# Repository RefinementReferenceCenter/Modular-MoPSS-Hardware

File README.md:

# Modular-MoPSS-Hardware

This repository contains the necessary files for 3D printing and to order the ModMoPSS module PCBs (eagle)

(This is a work in progress)

The contents of this repository are distributed under the GNU General Public License v3.0

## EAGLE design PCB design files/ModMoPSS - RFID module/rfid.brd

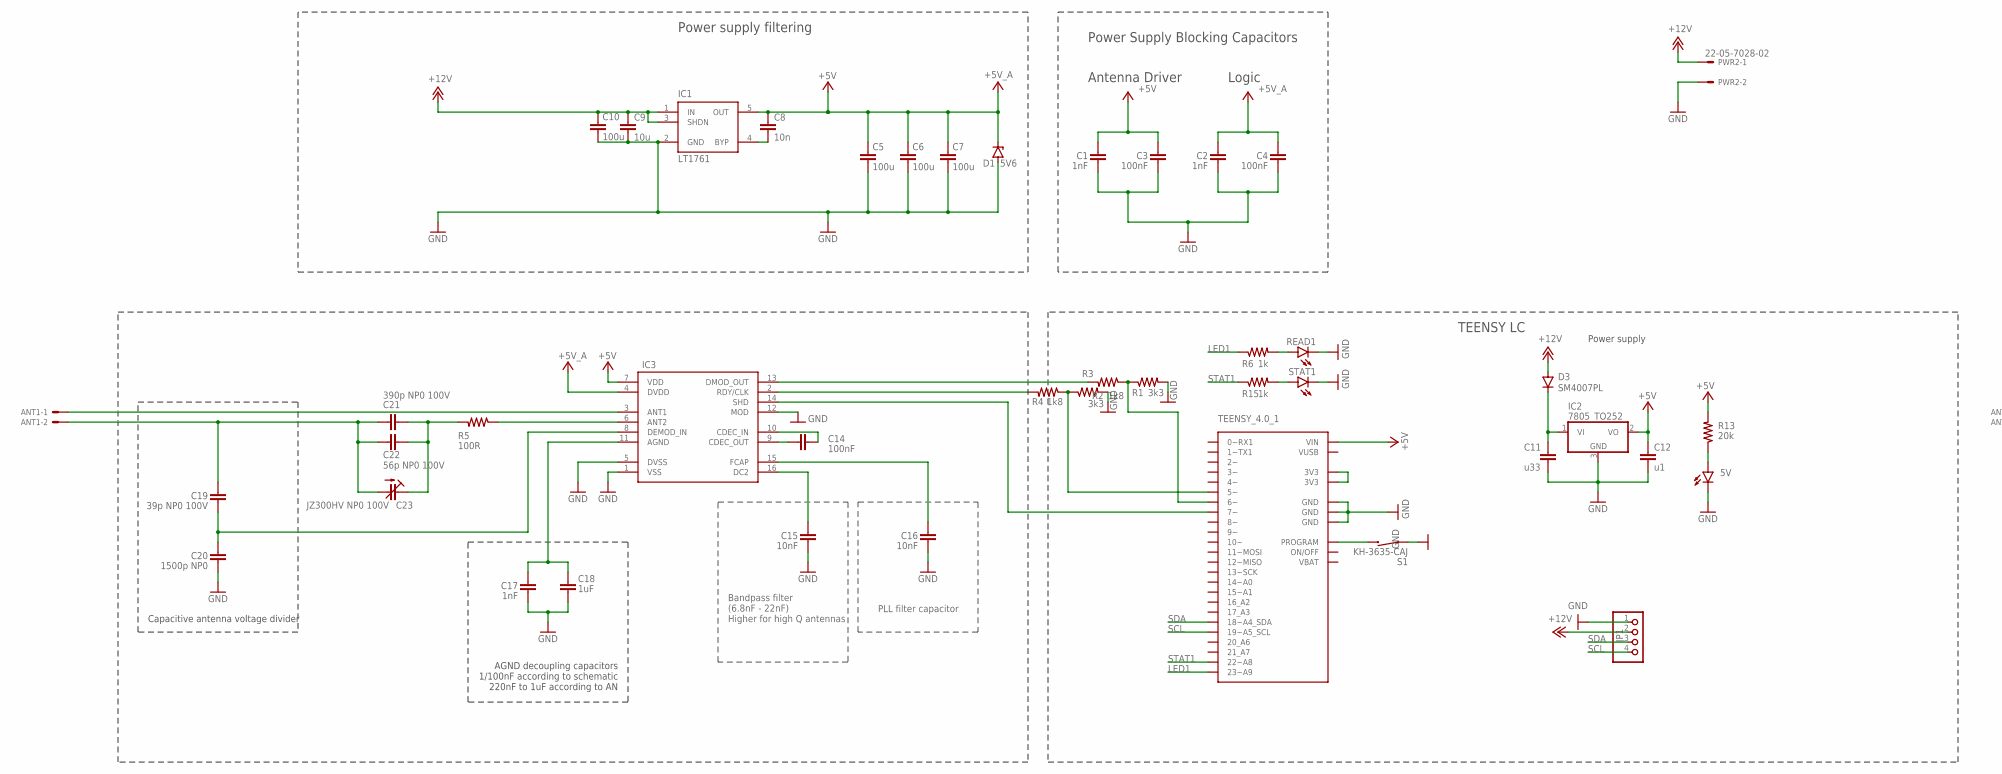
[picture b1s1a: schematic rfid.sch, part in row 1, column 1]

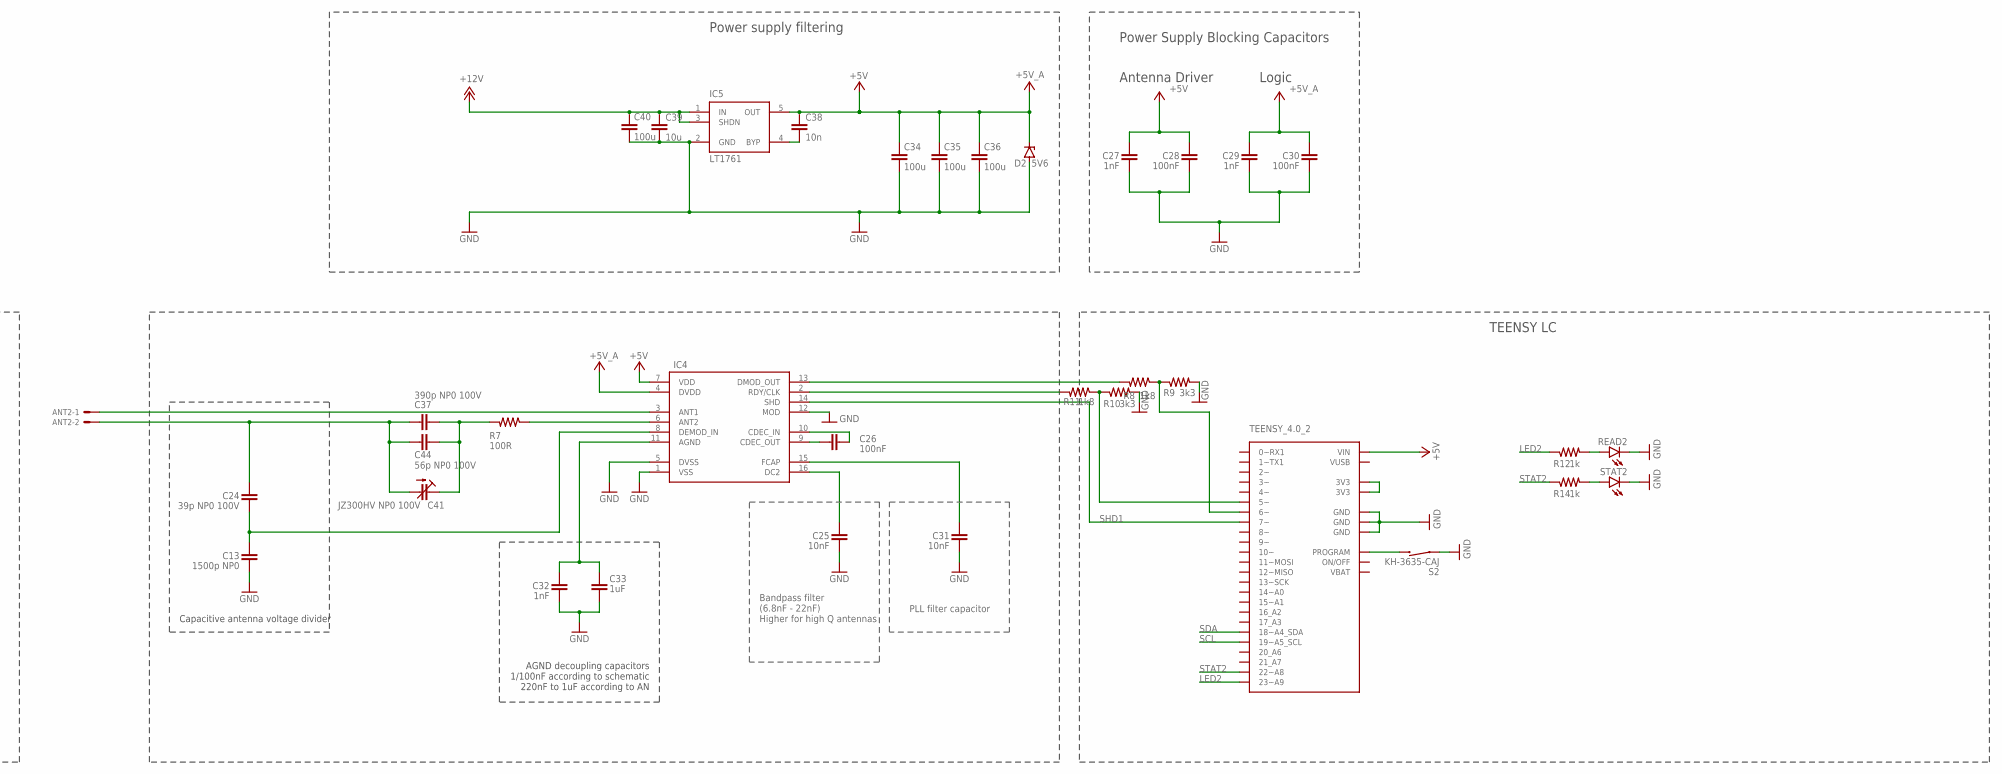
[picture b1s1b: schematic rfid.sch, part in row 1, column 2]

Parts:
5V: LEDCHIPLED_0805; CHIPLED_0805
ANT1, ANT2: 53261-02
C1, C2, C17, C27, C29, C32: 1nF; R1206
C3, C4, C14, C26, C28, C30: 100nF; R1206
C5, C6, C7, C10, C34, C35, C36, C40: 100u; R1206
C8, C38: 10n; R1206
C9, C39: 10u; R1206
C11: u33; C0805
C12: u1; C0805
C13, C20: 1500p NP0; R1206
C15, C16, C25, C31: 10nF; R1206
C18, C33: 1uF; R1206
C19, C24: 39p NP0 100V; R1206
C21, C37: 390p NP0 100V; R1206
C22, C44: 56p NP0 100V; R1206
C23, C41: JZ300HV NP0 100V; JZ300HV
D1, D2: 5V6; SOD80C
D3: SM4007PL; SOD-123_MINI-SMA
IC1, IC5: LT1761; TSOT23-5
IC2: 7805_TO252; TO252
IC3, IC4: EM4095; SO16
JP1: PINHD-1X4; 1X04
PWR2: 22-05-7028-02; 7395-02
R1, R3, R9, R10: 3k3; R0805
R2, R4, R8, R11: 1k8; R0805
R5, R7: 100R; R1206
R6, R12, R14, R15: 1k; R0805
R13: 20k; R0805
READ1, READ2: LEDCHIPLED_0805; CHIPLED_0805
S1, S2: KH-3635-CAJ
STAT1, STAT2: LEDCHIPLED_0805; CHIPLED_0805
TEENSY_4.0_1, TEENSY_4.0_2: TEENSY40

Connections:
+5V: C1.2, C2.2, C3.2, C4.2, C5.1, C6.1, C7.1, C8.1, C12.1, C27.2, C28.2, C29.2, C30.2, C34.1, C35.1, C36.1, C38.1, D1.C, D2.C, IC1.5 (OUT), IC2.2 (VO), IC3.4 (DVDD), IC3.7 (VDD), IC4.4 (DVDD), IC4.7 (VDD), IC5.5 (OUT), R13.2, TEENSY_4.0_1.VIN, TEENSY_4.0_2.VIN
+12V: C9.1, C10.1, C39.1, C40.1, D3.A, IC1.1 (IN), IC1.3 (SHDN), IC5.1 (IN), IC5.3 (SHDN), JP1.2, PWR2.1
AGND: C17.2, C18.2, IC3.11 (AGND)
AGND1: C32.2, C33.2, IC4.11 (AGND)
ANT2: IC3.6 (ANT2), R5.1
ANT3: IC4.6 (ANT2), R7.1
ANT4: ANT2.1, IC4.3 (ANT1)
CDEC_IN: C14.2, IC3.10 (CDEC_IN)
CDEC_IN1: C26.2, IC4.10 (CDEC_IN)
CDEC_OUT: C14.1, IC3.9 (CDEC_OUT)
CDEC_OUT1: C26.1, IC4.9 (CDEC_OUT)
DC1: C25.1, IC4.16 (DC2)
DC2: C15.1, IC3.16 (DC2)
DMODI: C19.1, C20.2, IC3.8 (DEMOD_IN)
DMODI1: C13.2, C24.1, IC4.8 (DEMOD_IN)
FCAP: C16.1, IC3.15 (FCAP)
FCAP1: C31.1, IC4.15 (FCAP)
GND: 5V.C, C1.1, C2.1, C3.1, C4.1, C5.2, C6.2, C7.2, C9.2, C10.2, C11.2, C12.2, C13.1, C15.2, C16.2, C17.1, C18.1, C20.1, C25.2, C27.1, C28.1, C29.1, C30.1, C31.2, C32.1, C33.1, C34.2, C35.2, C36.2, C39.2, C40.2, D1.A, D2.A, IC1.2 (GND), IC2.3 (GND), IC3.1 (VSS), IC3.5 (DVSS), IC3.12 (MOD), IC4.1 (VSS), IC4.5 (DVSS), IC4.12 (MOD), IC5.2 (GND), JP1.1, PWR2.2, R1.2, R3.2, R9.2, R10.2, READ1.C, READ2.C, S1.P$1 (1), S2.P$1 (1), STAT1.C, STAT2.C, TEENSY_4.0_1.GND, TEENSY_4.0_1.GND@1 (GND), TEENSY_4.0_1.GND@2 (GND), TEENSY_4.0_2.GND, TEENSY_4.0_2.GND@1 (GND), TEENSY_4.0_2.GND@2 (GND)
LED1: R6.1, TEENSY_4.0_1.23 (23~A9)
LED2: R12.1, TEENSY_4.0_2.23 (23~A9)
unnamed: R6.2, READ1.A
unnamed: R3.1, R4.1, TEENSY_4.0_1.5 (5~)
unnamed: ANT2.2, C24.2, C37.1, C41.P$1 (A), C44.1
unnamed: C37.2, C41.P$2 (E), C44.2, R7.2
unnamed: C21.2, C22.2, C23.P$2 (E), R5.2
unnamed: R1.1, R2.1, TEENSY_4.0_1.6 (6~)
unnamed: C8.2, IC1.4 (BYP)
unnamed: S1.P$2 (2), TEENSY_4.0_1.PROG (PROGRAM)
unnamed: C38.2, IC5.4 (BYP)
unnamed: TEENSY_4.0_1.3V3, TEENSY_4.0_1.3V3@2 (3V3)
unnamed: R8.1, R9.1, TEENSY_4.0_2.6 (6~)
unnamed: R10.1, R11.1, TEENSY_4.0_2.5 (5~)
unnamed: R12.2, READ2.A
unnamed: ANT1.2, C19.2, C21.1, C22.1, C23.P$1 (A)
unnamed: IC3.14 (SHD), TEENSY_4.0_1.7 (7~)
unnamed: S2.P$2 (2), TEENSY_4.0_2.PROG (PROGRAM)
unnamed: TEENSY_4.0_2.3V3, TEENSY_4.0_2.3V3@2 (3V3)
unnamed: R14.2, STAT2.A
unnamed: R15.2, STAT1.A
unnamed: ANT1.1, IC3.3 (ANT1)
unnamed: C11.1, D3.C, IC2.1 (VI)
unnamed: IC4.13 (DMOD_OUT), R8.2
unnamed: IC3.2 (RDY/CLK), R4.2
unnamed: IC3.13 (DMOD_OUT), R2.2
unnamed: 5V.A, R13.1
unnamed: IC4.2 (RDY/CLK), R11.2
SCL: JP1.4, TEENSY_4.0_1.19 (19~A5_SCL), TEENSY_4.0_2.19 (19~A5_SCL)
SDA: JP1.3, TEENSY_4.0_1.18 (18~A4_SDA), TEENSY_4.0_2.18 (18~A4_SDA)
SHD1: IC4.14 (SHD), TEENSY_4.0_2.7 (7~)
STAT1: R15.1, TEENSY_4.0_1.22 (22~A8)
STAT2: R14.1, TEENSY_4.0_2.22 (22~A8)

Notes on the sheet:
Power supply filtering
Antenna Driver
Logic
AGND decoupling capacitors 1/100nF according to schematic 220nF to 1uF according to AN
Capacitive antenna voltage divider
Bandpass filter (6.8nF - 22nF) Higher for high Q antennas
PLL filter capacitor
Power Supply Blocking Capacitors
TEENSY LC
Power supply

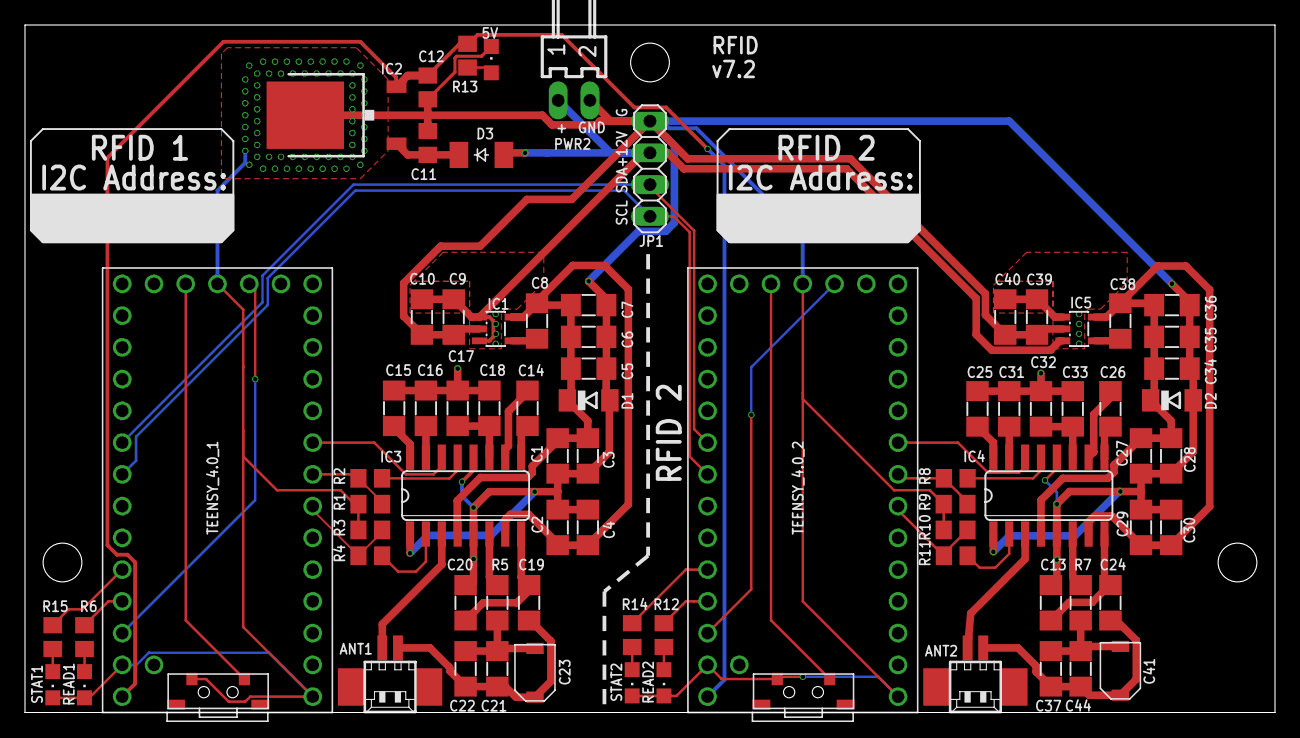
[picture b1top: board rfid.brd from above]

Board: 2 copper layers, 100.0 x 55.0 mm, 78 parts (0 on the bottom side), 51 nets.

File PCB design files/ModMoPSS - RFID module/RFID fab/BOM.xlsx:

Comment | Designator | Footprint | JLCPCB Part #（optional）
red | 5V, READ1, READ2, STAT1, STAT2 | CHIPLED_0805 | C84256
100R 100V | R5, R7 | R1206 | C17901
100nF | C3, C4, C14, C26, C28, C30 | R1206 | C24497
100u 6.3V | C5, C6, C7, C10, C34, C35, C36, C40 | R1206 | C15008
10n | C8, C38 | R1206 | C1846
10nF | C15, C16, C25, C31 | R1206 | C1846
10u 16V | C9, C39 | R1206 | C2911415
1500p NP0 | C13, C20 | R1206 | C309500
1k | R6, R12, R14, R15 | R0805 | C17513
1k8 | R2, R4, R8, R11 | R0805 | C17398
1nF | C1, C2, C17, C27, C29, C32 | R1206 | C9196
1uF | C18, C33 | R1206 | C1848
20k | R13 | R0805 | C4328
390p NP0 100V | C21, C37 | R1206 | C527300
39p NP0 100V | C19, C24 | R1206 | C527287
3k3 | R1, R3, R9, R10 | R0805 | C26010
53048-02 | ANT1, ANT2 | 53048-02 | C505099
56p NP0 100V | C22, C44 | R1206 | C527289
5V6 | D1, D2 | SOD80C | C8062
7805_TO252 | IC2 | TO252 | C233417
EM4095 | IC3, IC4 | SO16 | C11356
JZ300HV | C23, C41 | JZ300HV
KH-3635-CAJ | S1, S2 | KH-3635-CAJ | C530670
LT1761ES5-5 | IC1, IC5 | TSOT23-5 | C117230
u1 | C12 | C0805 | C49678
u33 | C11 | C0805 | C1740

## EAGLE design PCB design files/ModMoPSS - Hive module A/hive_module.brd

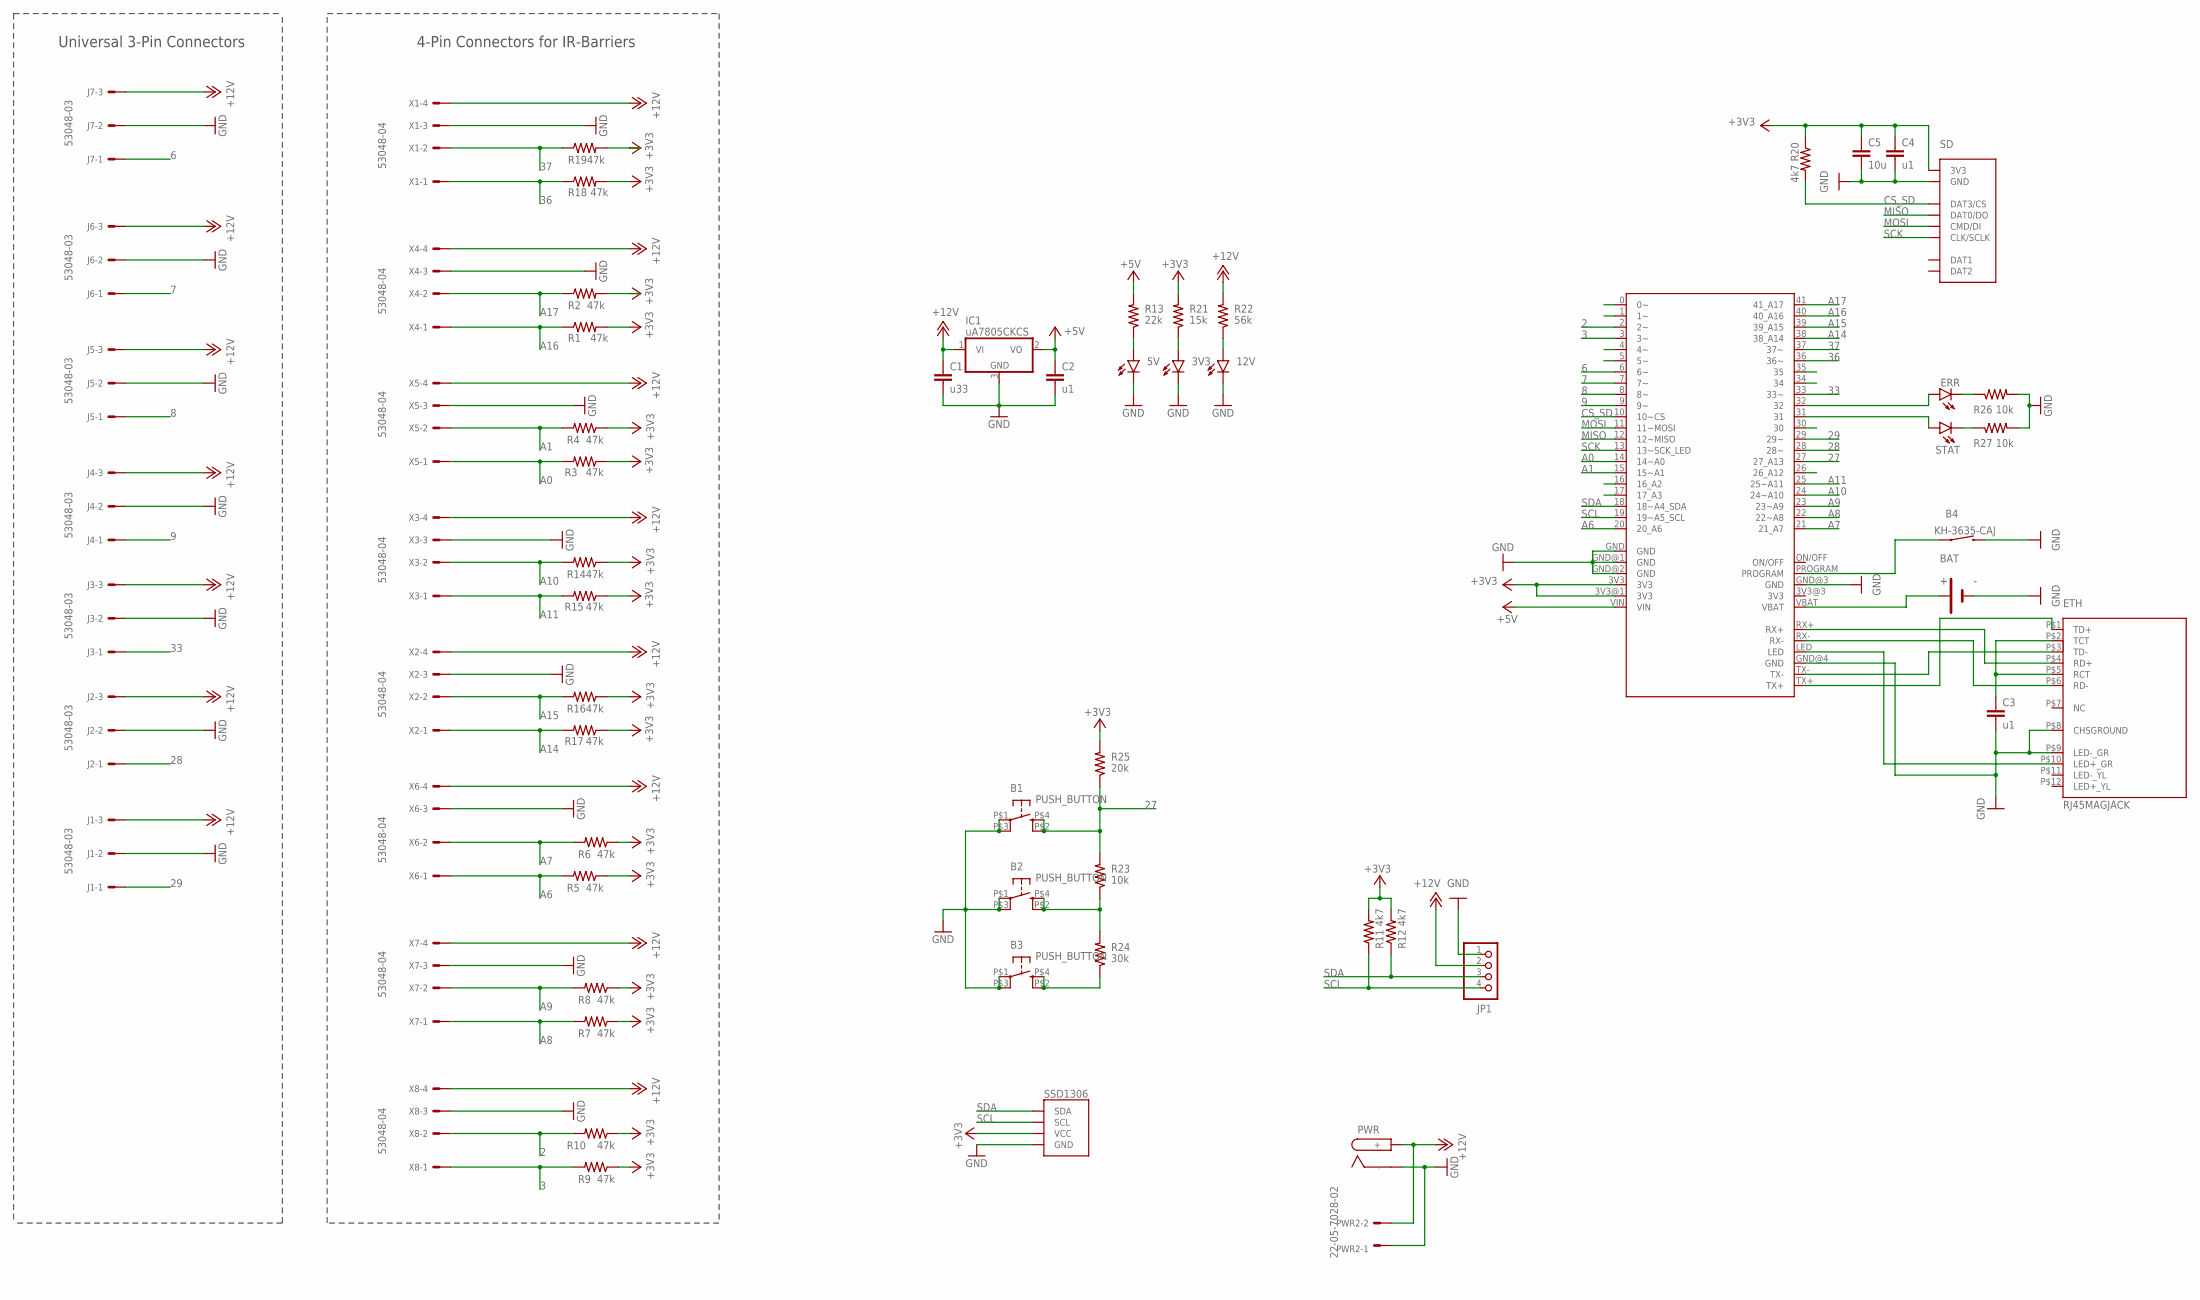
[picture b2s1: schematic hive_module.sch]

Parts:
3V3, 5V, 12V: LEDCHIP-LED0805; CHIP-LED0805
B1, B2, B3: PUSH_BUTTON
B4: KH-3635-CAJ
BAT: BS-08-B2AA002
C1: u33; C0805
C2, C3, C4: u1; C0805
C5: 10u; C0805
ERR: LEDCHIP-LED0805; CHIP-LED0805
ETH: RJ45MAGJACK; LPJ4012AHNL
IC1: uA7805CKCS; TO252
J1, J2, J3, J4, J5, J6, J7: 53048-03
JP1: PINHD-1X4; 1X04
PWR: DC-042C-Z-2.5-A
PWR2: 22-05-7028-02; 7395-02
R1, R2, R3, R4, R5, R6, R7, R8, R9, R10, R14, R15, R16, R17, R18, R19: 47k; R0805
R11, R12, R20: 4k7; R0805
R13: 22k; R0805
R21: 15k; R0805
R22: 56k; R0805
R23, R26, R27: 10k; R0805
R24: 30k; R0805
R25: 20k; R0805
SD: TF-011
SSD1306: SSD1306
STAT: LEDCHIP-LED0805; CHIP-LED0805
U$1: TEENSY41
X1, X2, X3, X4, X5, X6, X7, X8: 53048-04

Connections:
2: R10.2, U$1.2 (2~), X8.2
3: R9.2, U$1.3 (3~), X8.1
6: J7.1, U$1.6 (6~)
7: J6.1, U$1.7 (7~)
8: J5.1, U$1.8 (8~)
9: J4.1, U$1.9 (9~)
27: B1.P$2 (S1), B1.P$4 (S), R23.2, R25.1, U$1.27 (27_A13)
28: J2.1, U$1.28 (28~)
29: J1.1, U$1.29 (29~)
33: J3.1, U$1.33 (33~)
36: R18.1, U$1.36 (36~), X1.1
37: R19.1, U$1.37 (37~), X1.2
+3V3: C4.1, C5.1, R1.2, R2.2, R3.1, R4.1, R5.1, R6.1, R7.1, R8.1, R9.1, R10.1, R11.2, R12.2, R14.1, R15.1, R16.1, R17.1, R18.2, R19.2, R20.1, R21.2, R25.2, SD.P$4 (3V3), SSD1306.P$2 (VCC), U$1.3V3, U$1.3V3@1 (3V3)
+5V: C2.1, IC1.2 (VO), R13.2, U$1.VIN
+12V: C1.1, IC1.1 (VI), J1.3, J2.3, J3.3, J4.3, J5.3, J6.3, J7.3, JP1.2, PWR.P$6 (+), PWR2.2, R22.2, X1.4, X2.4, X3.4, X4.4, X5.4, X6.4, X7.4, X8.4
A0: R3.2, U$1.14 (14~A0), X5.1
A1: R4.2, U$1.15 (15~A1), X5.2
A6: R5.2, U$1.20 (20_A6), X6.1
A7: R6.2, U$1.21 (21_A7), X6.2
A8: R7.2, U$1.22 (22~A8), X7.1
A9: R8.2, U$1.23 (23~A9), X7.2
A10: R14.2, U$1.24 (24~A10), X3.2
A11: R15.2, U$1.25 (25~A11), X3.1
A14: R17.2, U$1.38 (38_A14), X2.1
A15: R16.2, U$1.39 (39_A15), X2.2
A16: R1.1, U$1.40 (40_A16), X4.1
A17: R2.1, U$1.41 (41_A17), X4.2
CS_SD: R20.2, SD.P$2 (DAT3/CS), U$1.10 (10~CS)
GND: 3V3.C, 5V.C, 12V.C, B1.P$1, B1.P$3 (P1), B2.P$1, B2.P$3 (P1), B3.P$1, B3.P$3 (P1), B4.P$2 (2), BAT.-, C1.2, C2.2, C3.2, C4.2, C5.2, ETH.P$8 (CHSGROUND), ETH.P$9 (LED-_GR), IC1.3 (GND), J1.2, J2.2, J3.2, J4.2, J5.2, J6.2, J7.2, JP1.1, PWR.P$1 (-), PWR.P$2 (-), PWR.P$3 (-), PWR.P$4 (-), PWR.P$5 (-), PWR2.1, R26.2, R27.2, SD.P$6 (GND), SD.P$9 (GND), SD.P$10 (GND), SD.P$11 (GND), SD.P$12 (GND), SSD1306.P$1 (GND), U$1.GND, U$1.GND@1 (GND), U$1.GND@2 (GND), U$1.GND@3 (GND), U$1.GND@4 (GND), X1.3, X2.3, X3.3, X4.3, X5.3, X6.3, X7.3, X8.3
MISO: SD.P$7 (DAT0/DO), U$1.12 (12~MISO)
MOSI: SD.P$3 (CMD/DI), U$1.11 (11~MOSI)
unnamed: ETH.P$1 (TD+), U$1.TX+
unnamed: ETH.P$3 (TD-), U$1.TX-
unnamed: 3V3.A, R21.1
unnamed: ETH.P$6 (RD-), U$1.RX-
unnamed: ETH.P$4 (RD+), U$1.RX+
unnamed: ETH.P$10 (LED+_GR), U$1.LED
unnamed: 12V.A, R22.1
unnamed: C3.1, ETH.P$2 (TCT), ETH.P$5 (RCT)
unnamed: BAT.+, U$1.VBAT
unnamed: B4.P$1 (1), U$1.PROGRAM
unnamed: ERR.A, U$1.32
unnamed: B3.P$2 (S1), B3.P$4 (S), R24.1
unnamed: B2.P$2 (S1), B2.P$4 (S), R23.1, R24.2
unnamed: ERR.C, R26.1
unnamed: R27.1, STAT.C
unnamed: STAT.A, U$1.31
unnamed: 5V.A, R13.1
SCK: SD.P$5 (CLK/SCLK), U$1.13 (13~SCK_LED)
SCL: JP1.4, R11.1, SSD1306.P$3 (SCL), U$1.19 (19~A5_SCL)
SDA: JP1.3, R12.1, SSD1306.P$4 (SDA), U$1.18 (18~A4_SDA)

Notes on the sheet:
4-Pin Connectors for IR-Barriers
Universal 3-Pin Connectors

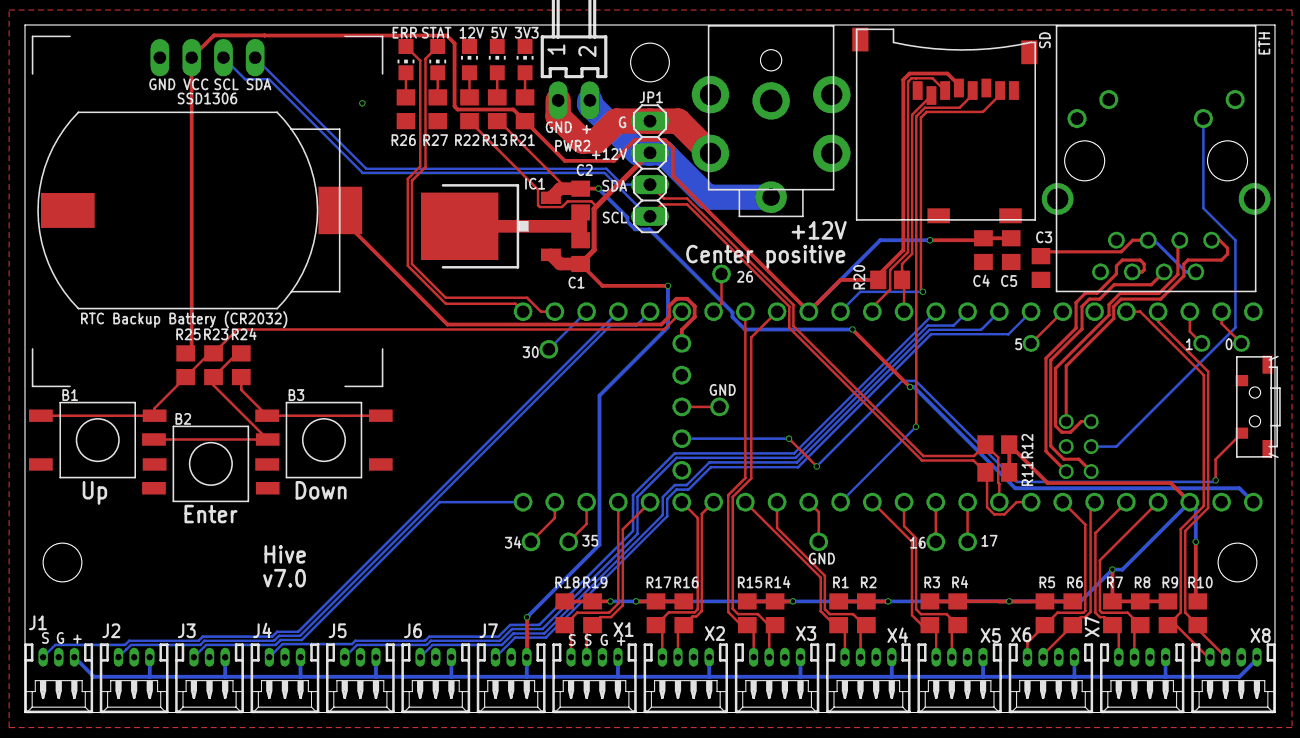
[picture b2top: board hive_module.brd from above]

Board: 2 copper layers, 100.0 x 55.0 mm, 65 parts (0 on the bottom side), 51 nets.

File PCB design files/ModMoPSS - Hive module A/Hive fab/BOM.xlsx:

Comment | Designator | Footprint | JLCPCB Part #（optional）
red | 3V3, 5V, 12V, ERR, STAT | CHIP-LED0805 | C84256
10k | R23, R26, R27 | R0805 | C17414
10u | C5 | C0805 | C15850
15k | R21 | R0805 | C17475
20k | R25 | R0805 | C4328
22k | R13 | R0805 | C17475
30k | R24 | R0805 | C17621
47k | R1, R2, R3, R4, R5, R6, R7, R8, R9, R10, R14, R15, R16, R17, R18, R19 | R0805 | C17713
4k7 | R11, R12, R20 | R0805 | C17673
53048-03 | J1, J2, J3, J4, J5, J6, J7 | 53048-03 | C505275
53048-04 | X1, X2, X3, X4, X5, X6, X7, X8 | 53048-04 | C588275
56k | R22 | R0805 | C17756
BS-08-B2AA002 | BAT | BS-08-B2AA002 | C964790
DC-042C-Z-2.5-A | PWR | DC-042C-Z-2.5-A | C706901
KH-3635-CAJ | B4 | KH-3635-CAJ | C530670
PUSH_BUTTON | B1, B2, B3 | PUSH_BUTTON | C127507
RJ45MAGJACK | ETH | LPJ4012AHNL | C910371
SSD1306 | SSD1306 | SSD1306 | C2718488
TF-011 | SD | TF-011 | C410352
u1 | C2, C3, C4 | C0805 | C49678
u33 | C1 | C0805 | C1740
uA7805CKCS | IC1 | TO252 | C233417

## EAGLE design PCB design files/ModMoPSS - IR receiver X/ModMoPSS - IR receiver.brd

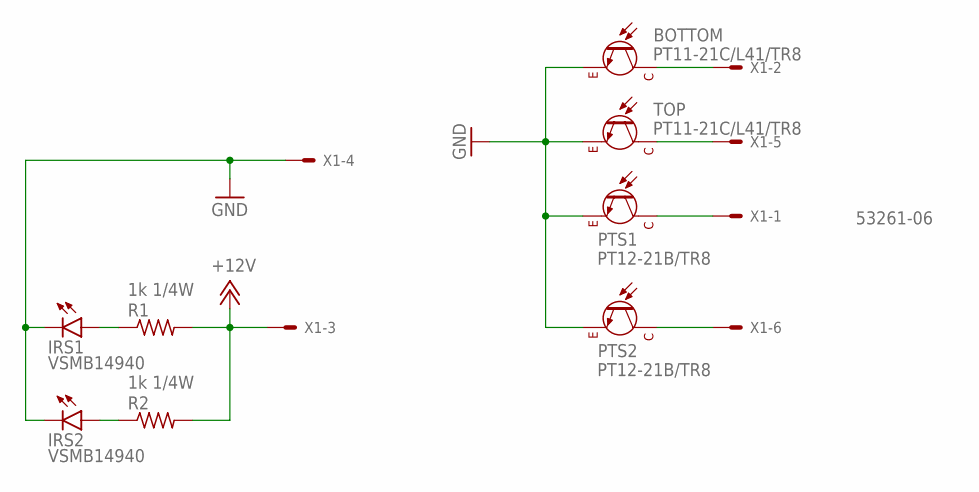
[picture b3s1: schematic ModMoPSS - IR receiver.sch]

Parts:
BOTTOM: PT11-21C/L41/TR8; CHIPLED_1206
IRS1, IRS2: VSMB14940
PTS1, PTS2: PT12-21B/TR8
R1, R2: 1k 1/4W; R0805
TOP: PT11-21C/L41/TR8; CHIPLED_1206
X1: 53261-06

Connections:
+12V: R1.2, R2.2, X1.3
GND: BOTTOM.A (E), IRS1.P$2 (C), IRS2.P$2 (C), PTS1.P$2 (E), PTS2.P$2 (E), TOP.A (E), X1.4
unnamed: BOTTOM.C, X1.2
unnamed: PTS1.P$1 (C), X1.1
unnamed: TOP.C, X1.5
unnamed: IRS2.P$1 (A), R2.1
unnamed: PTS2.P$1 (C), X1.6
unnamed: IRS1.P$1 (A), R1.1

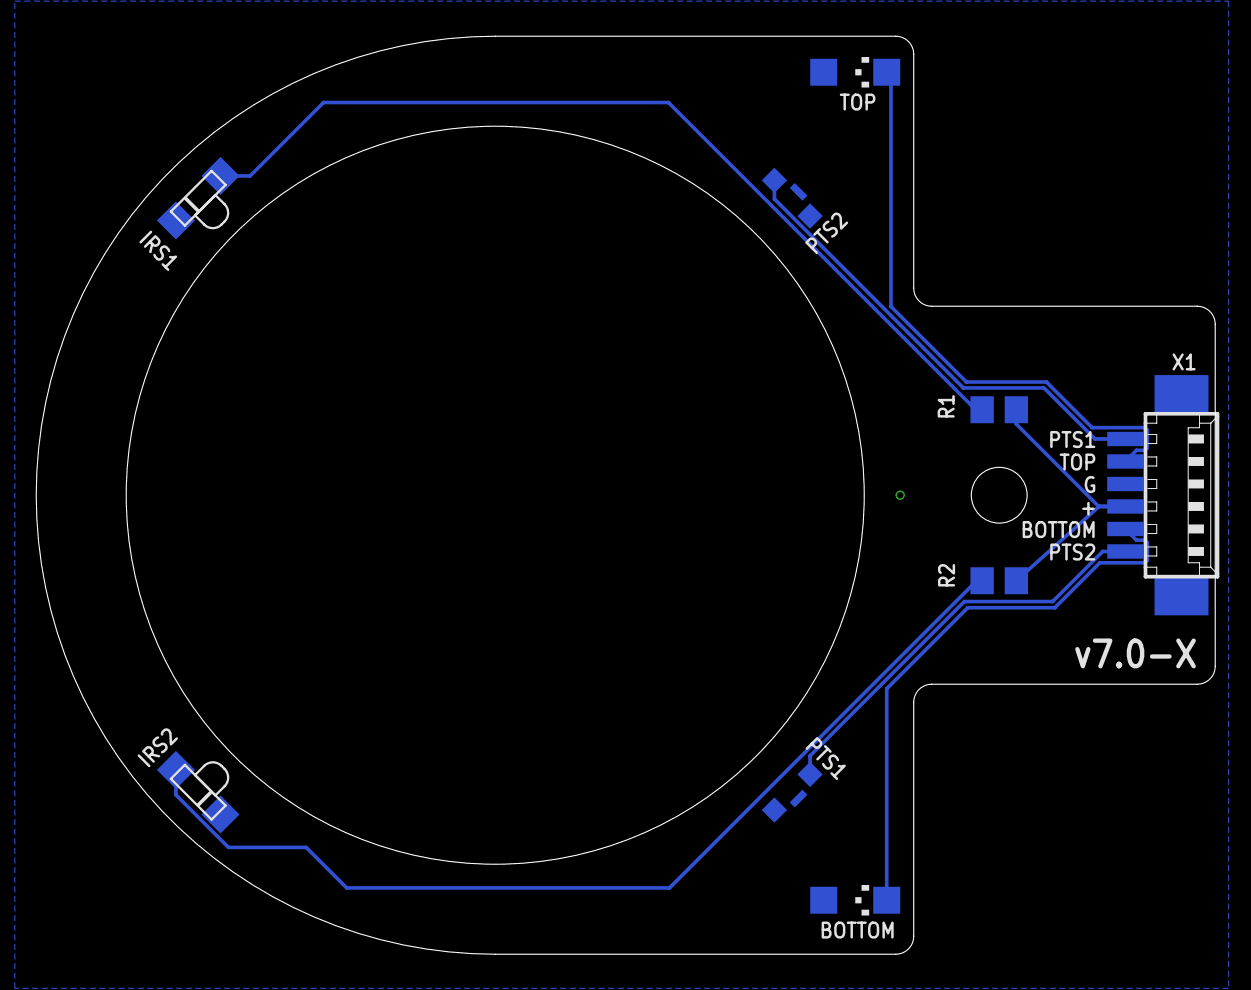
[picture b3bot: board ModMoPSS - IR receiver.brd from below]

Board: 2 copper layers, 65.5 x 51.0 mm, 9 parts (9 on the bottom side), 8 nets.

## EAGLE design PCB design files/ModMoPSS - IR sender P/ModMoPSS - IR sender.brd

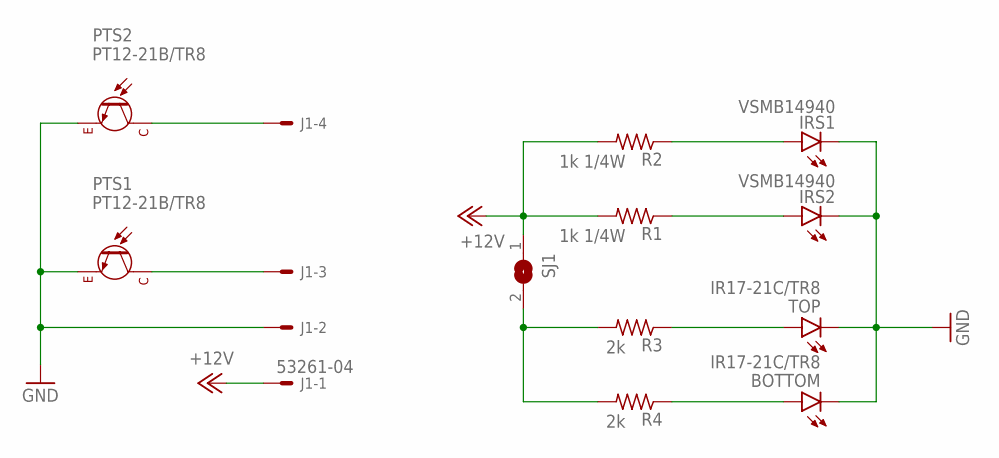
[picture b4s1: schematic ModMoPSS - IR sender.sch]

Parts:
BOTTOM: IR17-21C/TR8; CHIP-LED0805
IRS1, IRS2: VSMB14940
J1: 53261-04
PTS1, PTS2: PT12-21B/TR8
R1, R2: 1k 1/4W; R0805
R3, R4: 2k; R0805
SJ1: SJ
TOP: IR17-21C/TR8; CHIP-LED0805

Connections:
+12V: J1.1, R1.2, R2.2, SJ1.1
GND: BOTTOM.C, IRS1.P$2 (C), IRS2.P$2 (C), J1.2, PTS1.P$2 (E), PTS2.P$2 (E), TOP.C
unnamed: J1.3, PTS1.P$1 (C)
unnamed: IRS1.P$1 (A), R2.1
unnamed: BOTTOM.A, R4.1
unnamed: R3.1, TOP.A
unnamed: J1.4, PTS2.P$1 (C)
unnamed: R3.2, R4.2, SJ1.2
unnamed: IRS2.P$1 (A), R1.1

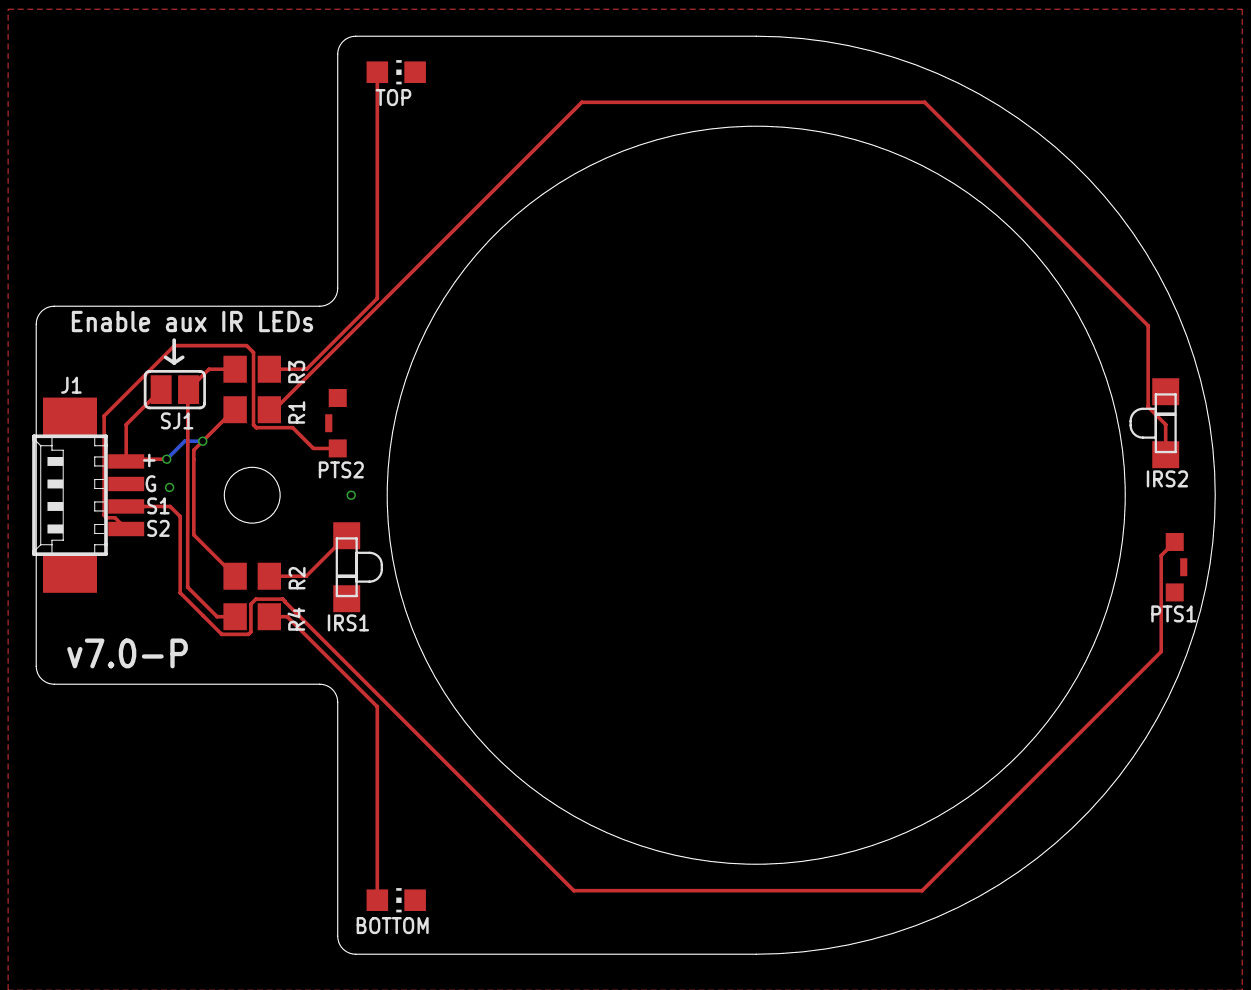
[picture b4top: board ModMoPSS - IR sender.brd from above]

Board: 2 copper layers, 65.5 x 51.0 mm, 12 parts (0 on the bottom side), 9 nets.

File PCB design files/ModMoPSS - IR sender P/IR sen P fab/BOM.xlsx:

Comment | Designator | Footprint | JLCPCB Part #（optional）
IR17-21C/TR8 | BOTTOM | CHIP-LED0805 | C131250
VSMB14940 | IRS1 | VSMB14940 | C511069
VSMB14940 | IRS2 | VSMB14940 | C511069
53261-04 | J1 | 53261-04 | C127368
PT12-21B/TR8 | PTS1 | PT12-21B/TR8 | C264383
PT12-21B/TR8 | PTS2 | PT12-21B/TR8 | C264383
1k 1/4W | R1 | R0805 | C412430
1k 1/4W | R2 | R0805 | C412430
2k | R3 | R0805 | C17604
2k | R4 | R0805 | C17604
IR17-21C/TR8 | TOP | CHIP-LED0805 | C131250

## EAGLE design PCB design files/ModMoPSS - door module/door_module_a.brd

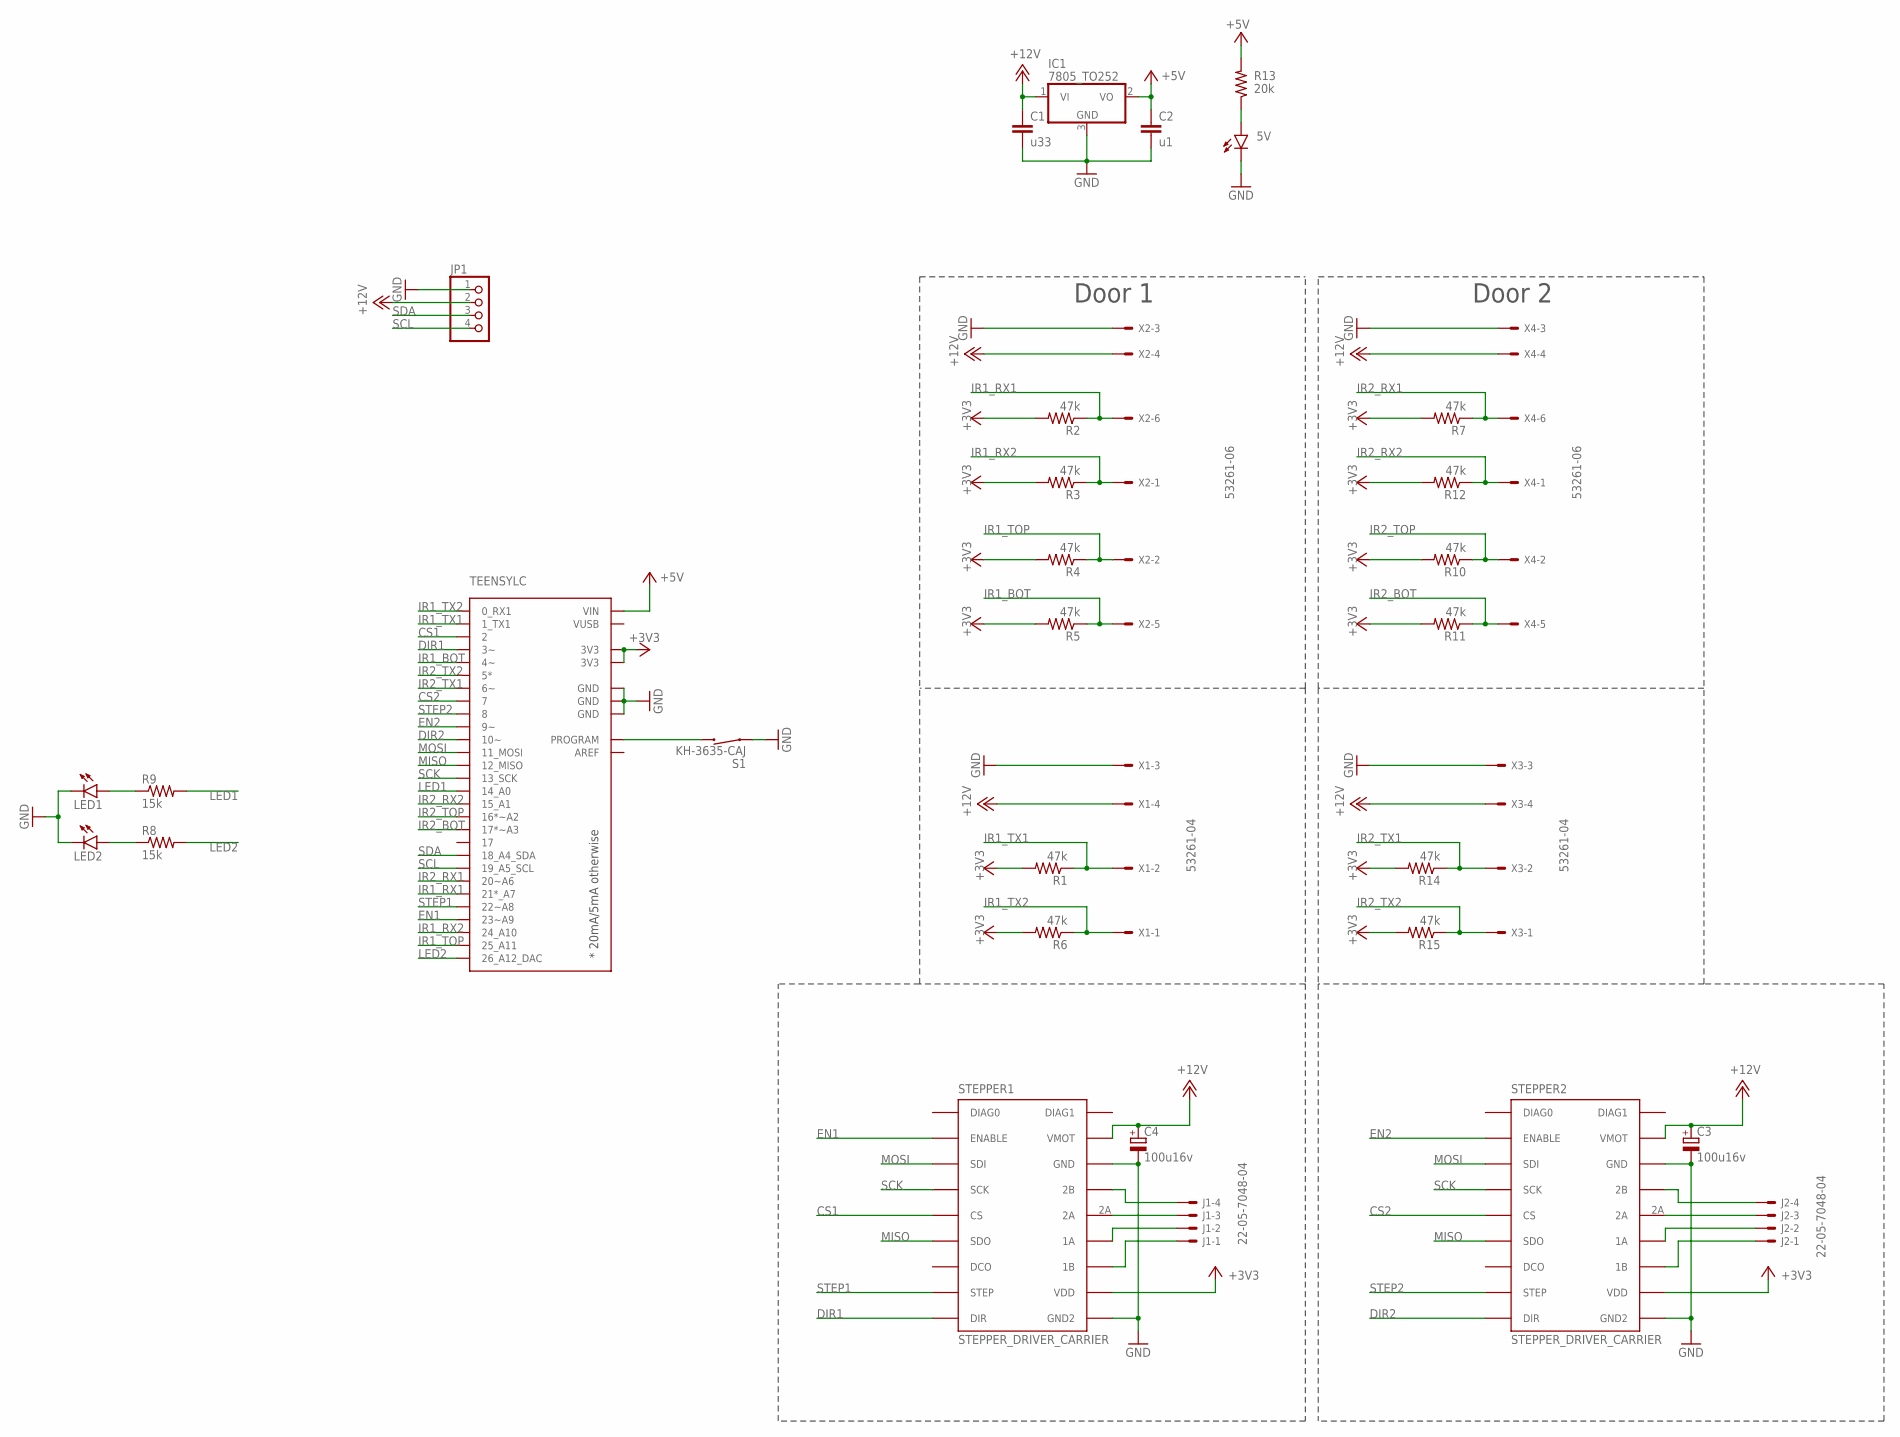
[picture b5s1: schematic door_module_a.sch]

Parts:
5V: LEDCHIPLED_0805; CHIPLED_0805
C1: u33; C0805
C2: u1; C0805
C3, C4: 100u16v; SMC_C
IC1: 7805_TO252; TO252
J1, J2: 22-05-7048-04; 7395-04
JP1: PINHD-1X4; 1X04
LED1, LED2: LEDCHIPLED_0805; CHIPLED_0805
R1, R2, R3, R4, R5, R6, R7, R10, R11, R12, R14, R15: 47k; R0805
R8, R9: 15k; R0805
R13: 20k; R0805
S1: KH-3635-CAJ
STEPPER1, STEPPER2: STEPPER_DRIVER_CARRIER; TMC2130_CARRIER
TEENSYLC: TEENSYLC
X1, X3: 53261-04
X2, X4: 53261-06

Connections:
+3V3: R1.2, R2.2, R3.2, R4.2, R5.2, R6.2, R7.2, R10.2, R11.2, R12.2, R14.2, R15.2, STEPPER1.VIO (VDD), STEPPER2.VIO (VDD), TEENSYLC.3V3, TEENSYLC.3V3@2 (3V3)
+5V: C2.1, IC1.2 (VO), R13.2, TEENSYLC.VIN
+12V: C1.1, C3.+, C4.+, IC1.1 (VI), JP1.2, STEPPER1.VMOT, STEPPER2.VMOT, X1.4, X2.4, X3.4, X4.4
CS1: STEPPER1.CS/CFG3 (CS), TEENSYLC.2
CS2: STEPPER2.CS/CFG3 (CS), TEENSYLC.7
DIR1: STEPPER1.DIR, TEENSYLC.3 (3~)
DIR2: STEPPER2.DIR, TEENSYLC.10 (10~)
EN1: STEPPER1.ENABLE, TEENSYLC.23 (23~A9)
EN2: STEPPER2.ENABLE, TEENSYLC.9 (9~)
GND: 5V.C, C1.2, C2.2, C3.-, C4.-, IC1.3 (GND), JP1.1, LED1.C, LED2.C, S1.P$1 (1), STEPPER1.GND, STEPPER1.GND2, STEPPER2.GND, STEPPER2.GND2, TEENSYLC.GND, TEENSYLC.GND@1 (GND), TEENSYLC.GND@2 (GND), X1.3, X2.3, X3.3, X4.3
IR1_BOT: R5.1, TEENSYLC.4 (4~), X2.5
IR1_RX1: R2.1, TEENSYLC.21 (21*_A7), X2.6
IR1_RX2: R3.1, TEENSYLC.24 (24_A10), X2.1
IR1_TOP: R4.1, TEENSYLC.25 (25_A11), X2.2
IR1_TX1: R1.1, TEENSYLC.1 (1_TX1), X1.2
IR1_TX2: R6.1, TEENSYLC.0 (0_RX1), X1.1
IR2_BOT: R11.1, TEENSYLC.17 (17*~A3), X4.5
IR2_RX1: R7.1, TEENSYLC.20 (20~A6), X4.6
IR2_RX2: R12.1, TEENSYLC.15 (15_A1), X4.1
IR2_TOP: R10.1, TEENSYLC.16 (16*~A2), X4.2
IR2_TX1: R14.1, TEENSYLC.6 (6~), X3.2
IR2_TX2: R15.1, TEENSYLC.5 (5*), X3.1
LED1: R9.2, TEENSYLC.14 (14_A0)
LED2: R8.2, TEENSYLC.26 (26_A12_DAC)
MISO: STEPPER1.SDO/CFG0 (SDO), STEPPER2.SDO/CFG0 (SDO), TEENSYLC.12 (12_MISO)
MOSI: STEPPER1.SDI/CFG1 (SDI), STEPPER2.SDI/CFG1 (SDI), TEENSYLC.11 (11_MOSI)
unnamed: LED2.A, R8.1
unnamed: LED1.A, R9.1
unnamed: S1.P$2 (2), TEENSYLC.PROG (PROGRAM)
unnamed: J1.4, STEPPER1.2B
unnamed: J1.3, STEPPER1.2A
unnamed: J1.2, STEPPER1.1A
unnamed: J2.2, STEPPER2.1A
unnamed: J1.1, STEPPER1.1B
unnamed: J2.4, STEPPER2.2B
unnamed: J2.3, STEPPER2.2A
unnamed: 5V.A, R13.1
unnamed: J2.1, STEPPER2.1B
SCK: STEPPER1.SCK/CFG2 (SCK), STEPPER2.SCK/CFG2 (SCK), TEENSYLC.13 (13_SCK)
SCL: JP1.4, TEENSYLC.19 (19_A5_SCL)
SDA: JP1.3, TEENSYLC.18 (18_A4_SDA)
STEP1: STEPPER1.STEP, TEENSYLC.22 (22~A8)
STEP2: STEPPER2.STEP, TEENSYLC.8

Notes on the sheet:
Door 1
Door 2
